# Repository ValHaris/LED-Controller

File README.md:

# LED-Controller

A small circuit board and software for controlling a set of LEDs based on an analogue input signal.

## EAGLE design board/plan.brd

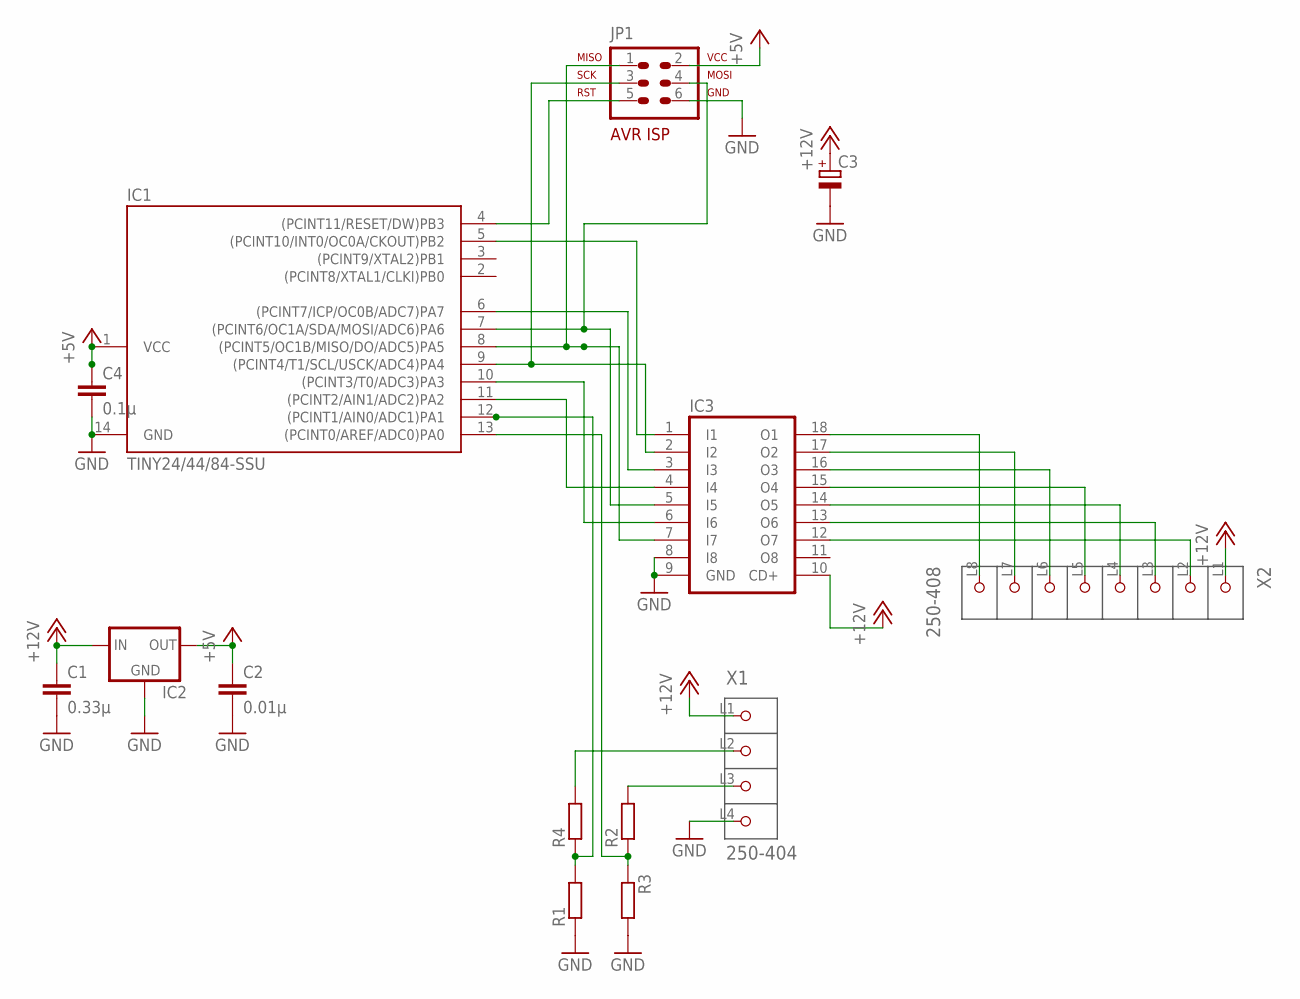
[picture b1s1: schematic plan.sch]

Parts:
C1: 0.33µ; C025-025X050
C2: 0.01µ; C025-025X050
C3: CPOL-EUSANYO_B; SANYO-OSCON_B
C4: 0.1µ; C025-030X050
IC1: TINY24/44/84-SSU; SOIC14
IC2: 78LXX
IC3: ULN2803ASMD; SO18W
JP1: AVR-ISP-6VERT; AVR-ISP-6
R1, R2, R3: R-EU_0204/2V; 0204V
R4: R-EU_0207/10; 0207/10
X1: 250-404; P-250-404
X2: 250-408; P-250-408

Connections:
+5V: C2.1, C4.1, IC1.1 (VCC), IC2.OUT, JP1.2
+12V: C1.1, C3.+, IC2.IN, IC3.10 (CD+), X1.L1 (P1), X2.L1 (P1)
GND: C1.2, C2.2, C3.-, C4.2, IC1.14 (GND), IC2.GND, IC3.8 (I8), IC3.9 (GND), JP1.6, R1.1, R3.2, X1.L4 (P4)
unnamed: R4.2, X1.L2 (P2)
unnamed: IC1.4 ((PCINT11/RESET/DW)PB3), JP1.5
unnamed: IC1.8 ((PCINT5/OC1B/MISO/DO/ADC5)PA5), IC3.7 (I7), JP1.1
unnamed: IC1.7 ((PCINT6/OC1A/SDA/MOSI/ADC6)PA6), IC3.5 (I5), JP1.4
unnamed: IC1.9 ((PCINT4/T1/SCL/USCK/ADC4)PA4), IC3.2 (I2), JP1.3
unnamed: IC1.5 ((PCINT10/INT0/OC0A/CKOUT)PB2), IC3.1 (I1)
unnamed: IC1.11 ((PCINT2/AIN1/ADC2)PA2), IC3.4 (I4)
unnamed: IC1.10 ((PCINT3/T0/ADC3)PA3), IC3.6 (I6)
unnamed: IC3.18 (O1), X2.L8 (P8)
unnamed: IC3.17 (O2), X2.L7 (P7)
unnamed: IC3.16 (O3), X2.L6 (P6)
unnamed: IC3.15 (O4), X2.L5 (P5)
unnamed: IC3.14 (O5), X2.L4 (P4)
unnamed: IC3.13 (O6), X2.L3 (P3)
unnamed: IC3.12 (O7), X2.L2 (P2)
unnamed: R2.2, X1.L3 (P3)
unnamed: IC1.12 ((PCINT1/AIN0/ADC1)PA1), R1.2, R4.1
unnamed: IC1.13 ((PCINT0/AREF/ADC0)PA0), R2.1, R3.1
unnamed: IC1.6 ((PCINT7/ICP/OC0B/ADC7)PA7), IC3.3 (I3)

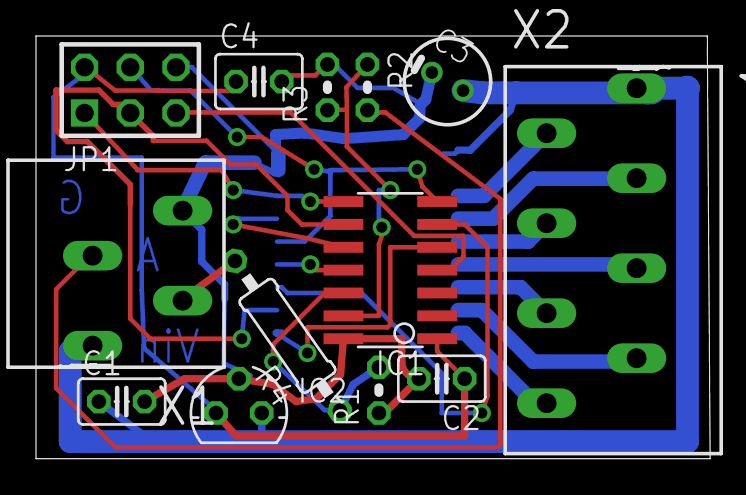
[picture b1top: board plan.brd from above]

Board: 2 copper layers, 37.5 x 23.5 mm, 14 parts (1 on the bottom side), 22 nets.

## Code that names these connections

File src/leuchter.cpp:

/*  Phaser MK3 main program
    Copyright 2009 by M. Bickel

    This program is free software: you can redistribute it and/or modify
    it under the terms of the GNU General Public License as published by
    the Free Software Foundation, either version 3 of the License, or
    (at your option) any later version.

    This program is distributed in the hope that it will be useful,
    but WITHOUT ANY WARRANTY; without even the implied warranty of
    MERCHANTABILITY or FITNESS FOR A PARTICULAR PURPOSE.  See the
    GNU General Public License for more details.

    You should have received a copy of the GNU General Public License
    along with this program.  If not, see http://www.gnu.org/licenses/
*/


#include <avr/io.h>
#include <stdint.h>
#include <avr/interrupt.h>
#include <avr/sleep.h>

#include "adc.h"
#include "output.h"
#include "inputfilter.h"

Output output;



struct Timer {
    typedef uint16_t Type;
    static inline Type getTime() {
        return TCNT1;
    }
    static inline void setTime( Type time ) {
        TCNT1 = time;
    }
};



void runLights()
{
    static uint8_t light = 255;

    static const uint16_t lightPattern[9] = { 0, 24, 36, 66, 129, 129<<8,66<<8,36<<8,24<<8 };

    static Timer::Type lastTime;

    if ( light == 255 ) {
        lastTime = TCNT1;
        light = 0;
    }

    if ( Timer::getTime() - lastTime > 210 ) {
        ++light;
        if ( light > 8 )
            light = 0;
        lastTime = Timer::getTime();
    }

    for ( uint8_t i = 0; i < Output::ledNum; ++i )
        output.setLED( i, !(lightPattern[light] & (1<<i) ));
}


class Debug {
public:
	Debug() {
		DDRA |= 1<<PA1;
		setValue(0);
	}
	void setValue( bool value ) {
		if ( value )
			PORTA &= ~(1<<PA1);
		else
			PORTA |= 1 << PA1;
	}
} debug;

typedef InputFilter<SingleChannelADConverter<0,2> > Input;

Input input;


class PWM0 {
public:
    PWM0() {
        TCCR0A = (TCCR0A & ~7) + 3; // Fast PWM Mode 	, counting to 0xff

        // Clear OC0A on Compare Match
        // Set OC0A at BOTTOM (non-inverting mode)
        TCCR0A |= 1 << COM0A1;
        TCCR0A &= ~(1 << COM0A0);

        TCCR0A |= 1 << COM0B1;
        TCCR0A &= ~(1 << COM0B0);


        // clock prescaled by 8
        TCCR0B &= ~((1<< CS02) | (1<<CS00));
        TCCR0B |= (1<<CS01);

        DDRB |= (1 << PB2); // output on OC0A
        DDRA |= (1 << PA7); // .. and OC0B
    }

    void setValue0A( uint8_t value) {
        OCR0A = value;
    }

    void setValue0B( uint8_t value ) {
        OCR0B = value;
    }
};

class PWM1 {
public:
    PWM1() {
        // Fast PWM, 8-bit
        TCCR1A |= (1 << WGM10);
        TCCR1A &= ~(1 << WGM11);
        TCCR1B |= 1 << WGM12;
        TCCR1B &= ~(1 << WGM13);

        // Clear OC0A on Compare Match
        // Set OC0A at BOTTOM (non-inverting mode)
        TCCR1A |= 1 << COM1A1;
        TCCR1A &= ~(1 << COM1A0);

        TCCR1A |= 1 << COM1B1;
        TCCR1A &= ~(1 << COM1B0);


        // clock prescaled by 8
        TCCR1B &= ~((1<< CS12) | (1<<CS10));
        TCCR1B |= (1<<CS11);

        DDRA |= (1 << PA6); // output on OC1A
        DDRA |= (1 << PA5); // .. and OC1B
    }

    void setValue1A( uint8_t value) {
        OCR1A = value;
    }

    void setValue1B( uint8_t value ) {
        OCR1B = value;
    }
};

static const uint8_t powersteps[Input::steps] = {
		0 * 0xff / (Input::steps-1),
		1 * 0xff / (Input::steps-1),
		2 * 0xff / (Input::steps-1),
		3 * 0xff / (Input::steps-1),
		4 * 0xff / (Input::steps-1),
		5 * 0xff / (Input::steps-1),
		6 * 0xff / (Input::steps-1),
		7 * 0xff / (Input::steps-1)
};

int main()
{
    PWM0 pulser;
    PWM1 pulser2;
    pulser.setValue0A(0);
    pulser.setValue0B(0);

    pulser2.setValue1A(0);
    pulser2.setValue1B(0);


    while(1) {

    	uint8_t value = input.run();
    	if ( value != 0 ) {
    		uint8_t power = powersteps[value-1];
    		pulser.setValue0A( power );
    		pulser.setValue0B(0xff - power );

    	    pulser2.setValue1A( power );
    	    pulser2.setValue1B(0xff - power );
    	    if ( value == 8 )
    	    	debug.setValue(1);
    	    else
    	    	debug.setValue(0);
    	}
    }

    return 0;
}

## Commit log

2016-01-07 added board and source code
2016-01-10 Fixed missing connection to ADC input
